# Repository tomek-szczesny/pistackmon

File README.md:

# PiStackMon

## What is it?

PiStackMon started off as a hardware module for distributing power to multiple stacked Raspberry Pi computers, rathen than handling multiple USB power adapters.

Over time, with its feature list open for new ideas, it grew into a highly integrated, multi purpose board with extended connectivity options.

The most eye catching feature is the live system monitor, with three most basic parameters (Temperature, RAM and CPU) clearly presented on a LED matrix. This helps quickly diagnosing performance bottlenecks by just looking at your cluster. LEDs are driven by a lightweight daemon, *pistackmond*, that compiles and runs on any target architecture.

PiStackMon comes with a variety of extra connectivity features, such as optically isolated outputs, isolated high current switches (up to 6A), dedicated fan output with suitable transistor, not to mention the usual I2C, UART or SPI.

Finally, PiStackMon allows you to power your SBC via GPIO pins, with additional polyfuse protection and a large capacitor, ensuring safe and stable operation. Screw terminals or barrel jack power inputs let you use any 5V power supply you wish, or even daisy chain a few units, thus sharing a common supply.

PiStackMon is compatible with any SBC following the RasPi GPIO layout. 

## Hardware

PiStackMon comes in two varieties, *lite* and *classic*.

### PiStackMon Lite

By popular demand, a new hardware version has been rolled out, offering the most useful subset of features seen in the Classic design. All mandatory SMD components are placed on top side, so the board may be ordered preassembled by JLCPCB. All required files are available in this repository.

The user is required to solder their own 40-pin socket, power switch pin header and power socket of their choice.

Features include:

- DC power input (either 5mm screw terminal or barrel jack)

- 2.5A Polyfuse protection

- 100uF ceramic capacitor

- Pin header for managing power supply (using a jumper or any other mechanical switch)

- 3x 5-LED indicators of real-time CPU usage, RAM usage and CPU temperature

- +5V LED indicator

- Extra user-programmable LED

- Soldering pads for accesing selected GPIOs:
  
  - I2C1
  
  - UART
  
  - GND, 3V3

- Two 0805 SMD placeholders for optional I2C1 pullup resistors

### PiStackMon Classic

The omnipotent, original design with all features available in the project. It is targeted at more advanced users, as no kits or preassembled units are available.

Alternatively, the schematic and KiCAD project files are available for reference. Feel free to modify it to suit your needs!

The design follows strict rules, so PCBs may be obtained for as low as 2 USD per 5 pieces at JLCPCB. 

- Supplying SBCs via screw terminals rather than USB port

- Dual power inputs-outputs allow clean and easy daisy-chaining

- 2.5A self-healing polyfuse protection 

- Bulk capacitor helps preventing transient undervoltage events

- Pin header for managing power supply (using a jumper or any other mechanical switch)

- +5V LED indicator

- 3x 5-LED indicators of real-time CPU usage, RAM usage and CPU temperature

- Auxiliary IOs for your projects:
  
  - SPI0, I2C1 and 1Wire easily accesible through 2.54mm headers
  
  - 1-Wire pullup resistor
  
  - 3-pin header with RC-filtered 3V3 supply for IR sensors
  
  - 2-pin header with 5V and BJT-reinforced low side switch, for PWM fan control
  
  - Two optically isolated outputs, for pulling external logic up or down (>2.5mA)
  
  - Two high-power, isolated low side switches, up to 26V and 6A
  
  - Alternatively, MCP1416s can be used as line drivers directly
  
  - Optical isolation lets you drive external circuits without creating ground loops
  
  - One isolated output and one high-power switch are connected to hardware PWM GPIO pins

- Low profile PCBs allow stacking with spacers as short as 20mm,

- No risk of contact with conductive stack spacers

- Components selected for low cost and relatively easy assembly (One TSSOP24 chip might be tricky)

- Alternative components are listed as well

- Modular design lets you build even cheaper boards without features you don't need

## Software

*pistackmond* is a lightweight daemon that's only purpose is to read system stats and drive PiStackMon LEDs. Additionally, it may be used by external software to drive the user-programmable LED available in PiStackMon Lite.

The recommended way to set up *pistackmond* on a target machine is to build it from source, in a few simple steps explained below. Alternatively, a DEB package may be built and distributed within your cluster.

*pistackmond* runs as a systemd service and has no dependencies outside standard C++ libraries. It has been tested on multiple Linux systems, including those based on Ubuntu, Debian or Arch.

#### Building pistackmond from source

- Log in to your SBC as any user with sudo access. 

- Install `git`, `g++` and `make`:
  
  - Debian, Ubuntu, RasPi OS etc:
    
    `sudo apt install git g++ make`
  
  - Arch, Manjaro and other derivatives:
    
    `sudo pacman -S git gcc make`

- Clone this repository:
  
  `git clone --depth 1 --branch main https://github.com/tomek-szczesny/pistackmon.git`

- Enter sw directory:
  
  - `cd pistackmon/sw`

- List build options to pick the right one for your SBC:
  
  - `make`

- Build pistackmond (Example for Raspberry Pi 4):
  
  - `make rpi4`

- Install and run systemd service
  
  - `sudo make install`

Note that you can change the default-brightness of LED-colors using the make
command, e.g. the following command changes the default 0.35 to 0.25.

    make rpi4 LED_G=0.25

The executable `pistackmond` supports various commandline arguments, see

    pistackmond -h

for a short help. Typically it is used to control the user-led (light version
only):

    pistackmond -u 1
    pistackmond -u 0
    pistackmond -u 0.4

The first command turns the blue user-led on, the second off and the third
turns it on with reduced brightness.

The `-b` option is used as a scaling factor for the overall brightness and
is only valid during service-startup. To set the factor for the service,
edit `/etc/default/pistackmond`.

That's it! PiStackMon should start displaying your computer stats immediately.

#### Creating a DEB-Package

In case you don't want to have a compiler and source code on your
production machines, you can create a deb-package on one system and
install it on multiple other systems.

The recommended procedure is:

```
apt-get -y install checkinstall  # if not already installed
cd pistackmon/sw
make clean                       # in case you don't start from scratch
#edit the `makefile` and replace `PREFIX=/usr/local` with `PREFIX=/usr`
make rpi4
sudo ./make-deb rpi4
```

This will create a package named `pistackmond-rpi4...deb`.

To install this package, run

```
dpkg -i pistackmond-rpi4...deb
sudo systemctl start pistackmond.service
```

## Compatible SBCs

PiStackMon is electrically compatible with all SBCs that follow the RasPi 40-pin GPIO layout. However, explicit support must be implemented in *pistackmond* daemon for that to work.

| SBC            | Status     | Remarks                                                                                                                                    |
| -------------- | ---------- | ------------------------------------------------------------------------------------------------------------------------------------------ |
| Raspberry Pi 3 | Compatible |                                                                                                                                            |
| Raspberry Pi 4 | Compatible |                                                                                                                                            |
| Odroid N2(+)(L)| Compatible | Powering via PiStackMon is not supported. Any attempt will likely destroy your N2.                                                         |
| Odroid C1(+)   | Compatible | Temperature sensing not confirmed. OS must export CPU temperature to the following file: `/sys/devices/virtual/thermal/thermal_zone0/temp` |
| Odroid C2      | Compatible | Powering via PiStackMon may be possible - not tested, proceed with caution.                                                                |
| Odroid M1      | Compatible | Powering via PiStackMon is not supported. Any attempt will likely destroy your M1.                                                         |

Limited amount of free PiStackMon samples is available for testers and contributors for new platforms. Open an Issue to get in touch!

# Disclaimer

This hardware and software is provided as-is.
All hardware and software presented in this repository may pose hazard to humans, animals, plants, fungi, ghosts, spirits and hardware, and is not guaranteed to work at all.
DO NOT ATTEMPT TO MAKE ANY USE OF FILES PROVIDED IN THIS REPOSITORY.

Users agree to take full responsibility for their actions involving files in this repository.
Ask an expert before you mess with stuff you don't understand.

# 

# Building PistackMon Classic

This chapter will definitely need some love, but for now just be sure to follow a few guidelines off the top of my head:

- Decide which features you need or not. As a rule of thumb, you may ignore any boxed part of a schematic independently.
- Check the datasheet of your LEDs or experiment to determine what is the optimal driving current for them. Some LEDs need 1mA, some 10mA. There are no recommended LEDs for PiStackMon.
- If different colors of your LEDs of choice have different intensities, don't worry, there are const values in the code to compensate for that.
- "NM" resistors are simply Not Mounted - leave these places empty, unlesss you want to hack PiStackMon for other purposes.
- Before you do anything, just remember that 40-pin connector should be mounted as the very last component, after you make sure everything else works. Consider it a permanent component, because removing it is indeed a pain in the rectum.
- Mount everything you plan to include, except 40-pin connector and C1. Power up your SBC using its original power input. You may test PiStackMon by carefully connecting it to SBC's GPIO header directly, and applying some tension to ensure proper connection. It is a good idea to check if all LEDs work correctly and that you picked the right LED currents.
- After soldering, make sure you clean your board _very carefully_ from any traces of flux, especially under and around the LED driver chip. Dip it in pure alcohol for an hour if you have to. Failing to do so may make some LEDs glow even though these are supposed to be off.
- Place a tiny heatsink on a low side high-power switch MOSFET if you plan to thrash the living hell out of it.

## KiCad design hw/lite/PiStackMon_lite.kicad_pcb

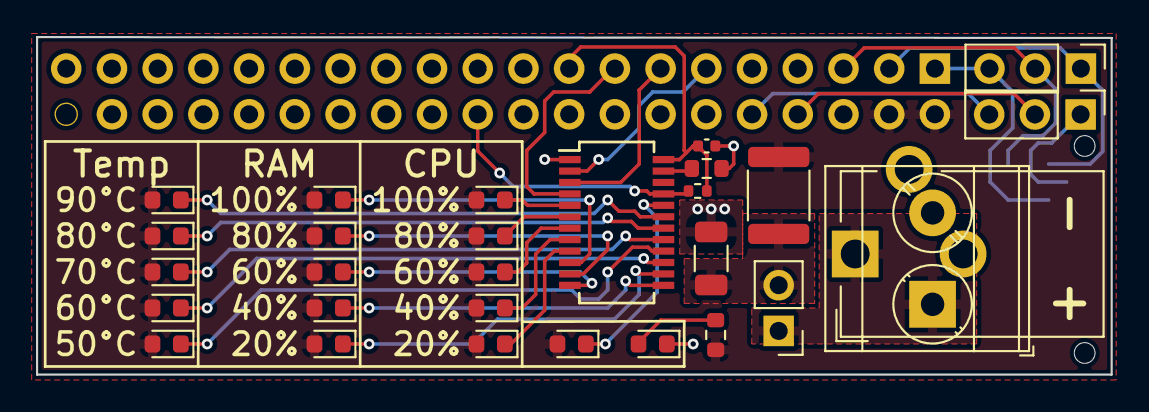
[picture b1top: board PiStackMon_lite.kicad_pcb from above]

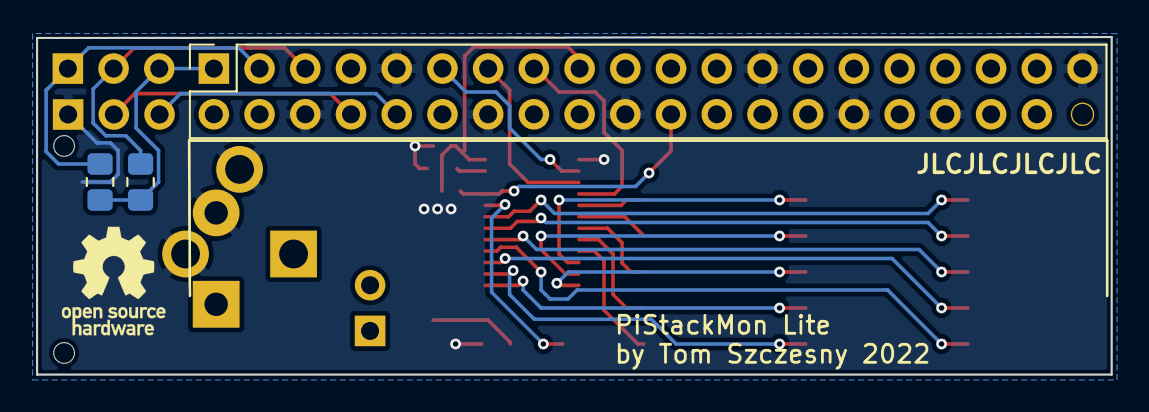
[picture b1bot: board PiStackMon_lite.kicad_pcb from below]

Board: 2 copper layers, 59.7 x 18.8 mm, 35 parts (4 on the bottom side), 32 nets.

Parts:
C1: 100u 6.3V; C_1206_3216Metric
C2: 100n; C_0402_1005Metric
D1, D2, D3, D4, D6, D7, D8, D14, D15, D16: G; LED_0603_1608Metric
D5, D9, D13: Y; LED_0603_1608Metric
D10, D11, D12: R; LED_0603_1608Metric
D17: B; LED_0603_1608Metric
F1: SMD1812B260TF/12; Fuse_1812_4532Metric
H1, H2: Tooling Hole
J1, J2: Conn_01x03; PinHeader_1x03_P2.54mm_Vertical
J3: 5.08mm; TerminalBlock_Phoenix_MKDS-3-2-5.08_1x02_P5.08mm_Horizontal
J5: CUI PJ-102; BarrelJack_CUI_PJ-102AH_Horizontal
JP1: PWR; PinHeader_1x02_P2.54mm_Vertical
LOGO1: Logo_Open_Hardware_Small; OSHW-Logo_5.7x6mm_SilkScreen
P1: Conn_02x20_Odd_Even; PinSocket_2x20_P2.54mm_Vertical
R1, R4: NM; R_0805_2012Metric_Pad1.20x1.40mm_HandSolder
R2: 10k; R_0603_1608Metric
R3: 560R; R_0603_1608Metric
R5: 3k3; R_0402_1005Metric
U1: TLC59282DBQR; SSOP-24_3.9x8.7mm_P0.635mm

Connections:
+3V3: C2.1, P1.17, R5.2, U1.24 (VDD)
+5V: D1.2 (A), D2.2 (A), D3.2 (A), D4.2 (A), D5.2 (A), D6.2 (A), D7.2 (A), D8.2 (A), D9.2 (A), D10.2 (A), D11.2 (A), D12.2 (A), D13.2 (A), D14.2 (A), D15.2 (A), D17.2 (A), F1.1, P1.2, P1.4, R3.1
+5VP: J3.1, J5.1, JP1.1 (A)
/3V3_2: J1.3, P1.1, R1.1, R4.1
/GPIO2(SDA1): J1.1, P1.3, R4.2
/GPIO3(SCL1): J1.2, P1.5, R1.2
/GPIO14(TXD0): J2.2, P1.8
/GPIO15(RXD0): J2.3, P1.10
/GPIO17(GEN0): P1.11, U1.2 (SDI)
/GPIO22(GEN3): P1.15, U1.4 (LE/DM1)
/GPIO25(GEN6): P1.22, R5.1, U1.21 (~OE/DM2)
/GPIO27(GEN2): P1.13, U1.3 (CLK)
GND: C1.2, C2.2, D16.1 (K), J2.1, J3.2, J5.2, J5.3, P1.6, P1.9, P1.14, P1.20, P1.25, P1.30, P1.34, P1.39, R2.2, U1.1 (GND)
unnamed: C1.1, F1.2, JP1.2 (B)
unnamed: D1.1 (K), U1.9 (~OUT4)
unnamed: D2.1 (K), U1.8 (~OUT3)
unnamed: D3.1 (K), U1.7 (~OUT2)
unnamed: D4.1 (K), U1.6 (~OUT1)
unnamed: D5.1 (K), U1.5 (~OUT0)
unnamed: D6.1 (K), U1.14 (~OUT9)
unnamed: D7.1 (K), U1.13 (~OUT8)
unnamed: D8.1 (K), U1.12 (~OUT7)
unnamed: D9.1 (K), U1.11 (~OUT6)
unnamed: D10.1 (K), U1.10 (~OUT5)
unnamed: D11.1 (K), U1.19 (~OUT14)
unnamed: D12.1 (K), U1.18 (~OUT13)
unnamed: D13.1 (K), U1.17 (~OUT12)
unnamed: D14.1 (K), U1.15 (~OUT10)
unnamed: D15.1 (K), U1.16 (~OUT11)
unnamed: D16.2 (A), R3.2
unnamed: D17.1 (K), U1.20 (~OUT15)
unnamed: R2.1, U1.23 (R-EXT)

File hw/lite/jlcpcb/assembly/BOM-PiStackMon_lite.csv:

Comment,Designator,Footprint,LCSC
TLC59282DBQR,U1,SSOP-24_3.9x8.7mm_P0.635mm,C129352
100u 6.3V,C1,C_1206_3216Metric,C15008
100n,C2,C_0402_1005Metric,C1525
560R,R3,R_0603_1608Metric,C23204
10k,R2,R_0603_1608Metric,C25804
3k3,R5,R_0402_1005Metric,C25890
SMD1812B260TF/12,F1,Fuse_1812_4532Metric,C269147
Y,"D13,D5,D9",LED_0603_1608Metric,C72038
B,D17,LED_0603_1608Metric,C72041
G,"D1,D14,D15,D16,D2,D3,D4,D6,D7,D8",LED_0603_1608Metric,C72043
R,"D10,D11,D12",LED_0603_1608Metric,C72044

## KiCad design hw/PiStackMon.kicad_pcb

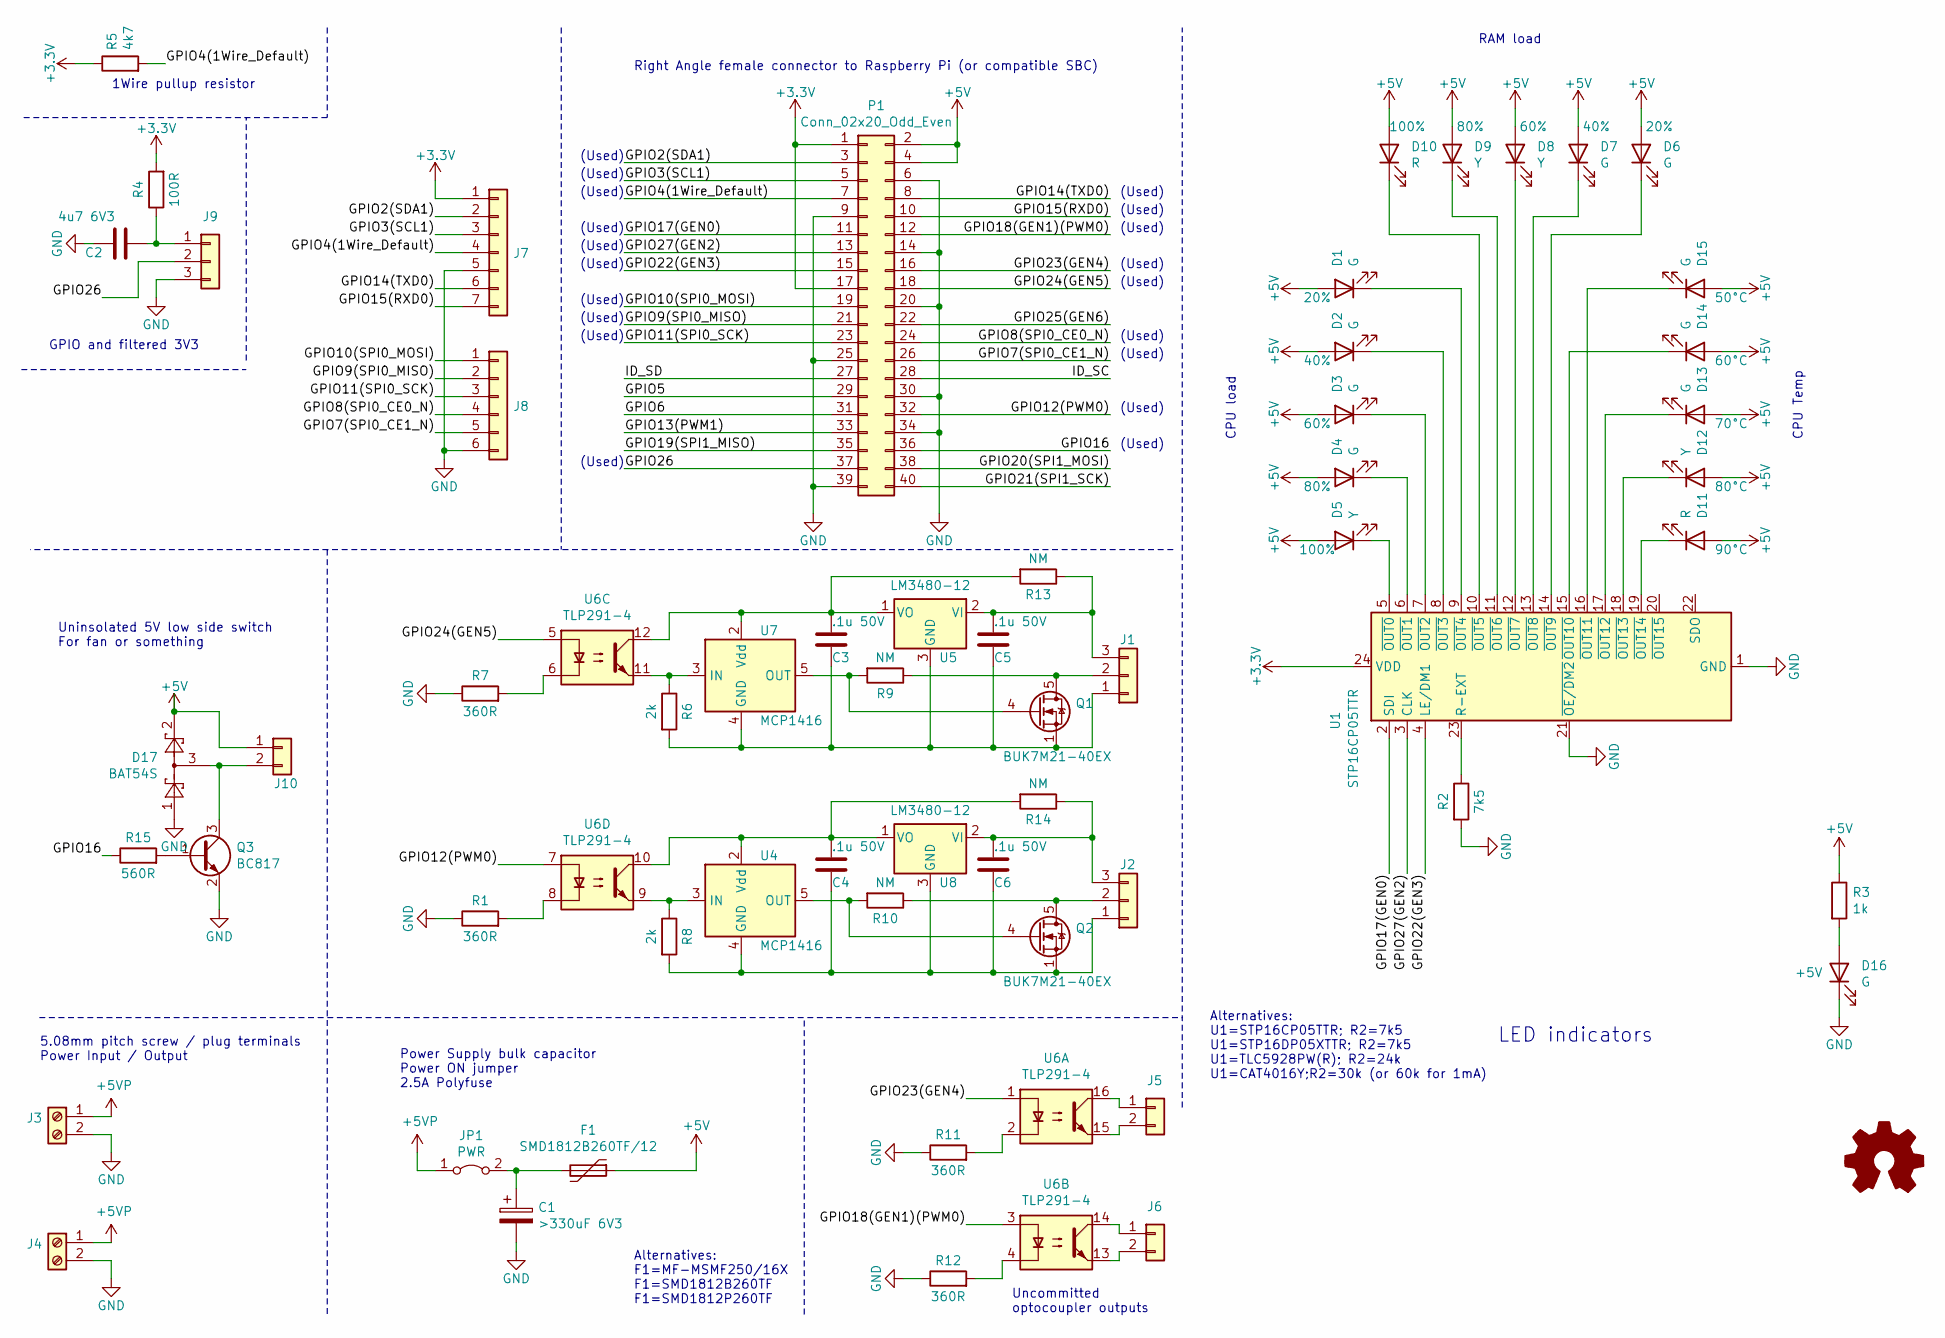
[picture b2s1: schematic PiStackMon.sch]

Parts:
C1: >330uF 6V3; CP_Radial_D8.0mm_P3.50mm
C2: 4u7 6V3; C_0603_1608Metric_Pad1.08x0.95mm_HandSolder; LCSC C8032
C3, C4, C5, C6: .1u 50V; C_0603_1608Metric_Pad1.08x0.95mm_HandSolder; LCSC C14663
D1, D2, D3, D4, D6, D7, D13, D14, D15, D16: G; LED_0603_1608Metric_Pad1.05x0.95mm_HandSolder; LCSC C72043
D5, D8, D9, D12: Y; LED_0603_1608Metric_Pad1.05x0.95mm_HandSolder; LCSC C72038
D10, D11: R; LED_0603_1608Metric_Pad1.05x0.95mm_HandSolder; LCSC C72044
D17: BAT54S; SOT-23; LCSC C47546
F1: SMD1812B260TF/12; Fuse_1812_4532Metric_Pad1.30x3.40mm_HandSolder; LCSC C269147
J1, J2, J9: Conn_01x03; PinHeader_1x03_P2.54mm_Vertical
J3, J4: Screw_Terminal_01x02; TerminalBlock_Phoenix_MKDS-3-2-5.08_1x02_P5.08mm_Horizontal
J5, J6, J10: Conn_01x02; PinHeader_1x02_P2.54mm_Vertical
J7: Conn_01x07; PinHeader_1x07_P2.54mm_Vertical
J8: Conn_01x05; PinHeader_1x06_P2.54mm_Vertical
JP1: PWR; PinHeader_1x02_P2.54mm_Vertical
LOGO1: Logo_Open_Hardware_Small; OSHW-Logo_5.7x6mm_SilkScreen
P1: Conn_02x20_Odd_Even; PinSocket_2x20_P2.54mm_Vertical
Q1, Q2: BUK7M21-40EX; LFPAK33
Q3: BC817; SOT-23; LCSC C52801
R1, R7, R11, R12: 360R; R_0603_1608Metric_Pad0.98x0.95mm_HandSolder; LCSC C25194
R2: 7k5; R_0603_1608Metric_Pad0.98x0.95mm_HandSolder; LCSC C23234
R3: 1k; R_0603_1608Metric_Pad0.98x0.95mm_HandSolder; LCSC C21190
R4: 100R; R_0603_1608Metric_Pad0.98x0.95mm_HandSolder; LCSC C22775
R5: 4k7; R_0603_1608Metric_Pad0.98x0.95mm_HandSolder; LCSC C23162
R6, R8: 2k; R_0603_1608Metric_Pad0.98x0.95mm_HandSolder; LCSC C22975
R9, R10, R13, R14: NM; R_0603_1608Metric_Pad0.98x0.95mm_HandSolder
R15: 560R; R_0603_1608Metric_Pad0.98x0.95mm_HandSolder; LCSC C23204
U1: STP16CP05TTR; TSSOP-24_4.4x7.8mm_P0.65mm; LCSC C127267
U4, U7: MCP1416; SOT-23-5; LCSC C83775
U5, U8: LM3480-12; SOT-23; LCSC C130175
U6: TLP291-4; SOIC-16_4.55x10.3mm_P1.27mm; LCSC C60900

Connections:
+3V3: J7.1, P1.1, P1.17, R4.2, R5.1, U1.24 (VDD)
+5V: D1.2 (A), D2.2 (A), D3.2 (A), D4.2 (A), D5.2 (A), D6.2 (A), D7.2 (A), D8.2 (A), D9.2 (A), D10.2 (A), D11.2 (A), D12.2 (A), D13.2 (A), D14.2 (A), D15.2 (A), D17.2, F1.1, J10.1, P1.2, P1.4, R3.1
+5VP: J3.1, J4.1, JP1.1 (A)
/GPIO2(SDA1): J7.2, P1.3
/GPIO3(SCL1): J7.3, P1.5
/GPIO4(1Wire_Default): J7.4, P1.7, R5.2
/GPIO5: P1.29
/GPIO6: P1.31
/GPIO7(SPI0_CE1_N): J8.5, P1.26
/GPIO8(SPI0_CE0_N): J8.4, P1.24
/GPIO9(SPI0_MISO): J8.2, P1.21
/GPIO10(SPI0_MOSI): J8.1, P1.19
/GPIO11(SPI0_SCK): J8.3, P1.23
/GPIO12(PWM0): P1.32, U6.7
/GPIO13(PWM1): P1.33
/GPIO14(TXD0): J7.6, P1.8
/GPIO15(RXD0): J7.7, P1.10
/GPIO16: P1.36, R15.1
/GPIO17(GEN0): P1.11, U1.2 (SDI)
/GPIO18(GEN1)(PWM0): P1.12, U6.3
/GPIO19(SPI1_MISO): P1.35
/GPIO20(SPI1_MOSI): P1.38
/GPIO21(SPI1_SCK): P1.40
/GPIO22(GEN3): P1.15, U1.4 (LE/DM1)
/GPIO23(GEN4): P1.16, U6.1
/GPIO24(GEN5): P1.18, U6.5
/GPIO25(GEN6): P1.22
/GPIO26: J9.2, P1.37
/GPIO27(GEN2): P1.13, U1.3 (CLK)
/ID_SC: P1.28
/ID_SD: P1.27
GND: C1.2, C2.2, D16.1 (K), D17.1, J3.2, J4.2, J7.5, J8.6, J9.3, P1.6, P1.9, P1.14, P1.20, P1.25, P1.30, P1.34, P1.39, Q3.2 (E), R1.1, R2.2, R7.1, R11.1, R12.1, U1.1 (GND), U1.21 (~OE/DM2)
unnamed: C1.1, F1.2, JP1.2 (B)
unnamed: C2.1, J9.1, R4.1
unnamed: C3.1, R13.2, U5.1 (VO), U6.12, U7.2 (Vdd)
unnamed: C3.2, C5.2, J1.1, Q1.1 (S), Q1.2 (S), Q1.3 (S), R6.2, U5.3 (GND), U7.4 (GND)
unnamed: C4.1, R14.2, U4.2 (Vdd), U6.10, U8.1 (VO)
unnamed: C4.2, C6.2, J2.1, Q2.1 (S), Q2.2 (S), Q2.3 (S), R8.2, U4.4 (GND), U8.3 (GND)
unnamed: C5.1, J1.3, R13.1, U5.2 (VI)
unnamed: C6.1, J2.3, R14.1, U8.2 (VI)
unnamed: D1.1 (K), U1.9 (~OUT4)
unnamed: D2.1 (K), U1.8 (~OUT3)
unnamed: D3.1 (K), U1.7 (~OUT2)
unnamed: D4.1 (K), U1.6 (~OUT1)
unnamed: D5.1 (K), U1.5 (~OUT0)
unnamed: D6.1 (K), U1.14 (~OUT9)
unnamed: D7.1 (K), U1.13 (~OUT8)
unnamed: D8.1 (K), U1.12 (~OUT7)
unnamed: D9.1 (K), U1.11 (~OUT6)
unnamed: D10.1 (K), U1.10 (~OUT5)
unnamed: D11.1 (K), U1.19 (~OUT14)
unnamed: D12.1 (K), U1.18 (~OUT13)
unnamed: D13.1 (K), U1.17 (~OUT12)
unnamed: D14.1 (K), U1.15 (~OUT10)
unnamed: D15.1 (K), U1.16 (~OUT11)
unnamed: D16.2 (A), R3.2
unnamed: D17.3, J10.2, Q3.3 (C)
unnamed: J1.2, Q1.5 (D), R9.1
unnamed: J2.2, Q2.5 (D), R10.1
unnamed: J5.1, U6.16
unnamed: J5.2, U6.15
unnamed: J6.1, U6.14
unnamed: J6.2, U6.13
unnamed: Q1.4 (G), R9.2, U7.5 (OUT)
unnamed: Q2.4 (G), R10.2, U4.5 (OUT)
unnamed: Q3.1 (B), R15.2
unnamed: R1.2, U6.8
unnamed: R2.1, U1.23 (R-EXT)
unnamed: R6.1, U6.11, U7.3 (IN)
unnamed: R7.2, U6.6
unnamed: R8.1, U4.3 (IN), U6.9
unnamed: R11.2, U6.2
unnamed: R12.2, U6.4

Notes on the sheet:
Right Angle female connector to Raspberry Pi (or compatible SBC)
5.08mm pitch screw / plug terminals Power Input / Output
Power Supply bulk capacitor Power ON jumper 2.5A Polyfuse
LED indicators
CPU load
RAM load
CPU Temp
(Used)
Uncommitted optocoupler outputs
1Wire pullup resistor
GPIO and filtered 3V3
Uninsolated 5V low side switch For fan or something
Alternatives: U1=STP16CP05TTR; R2=7k5 U1=STP16DP05XTTR; R2=7k5 U1=TLC5928PW(R); R2=24k U1=CAT4016Y;R2=30k (or 60k for 1mA)
Alternatives: F1=MF-MSMF250/16X F1=SMD1812B260TF F1=SMD1812P260TF

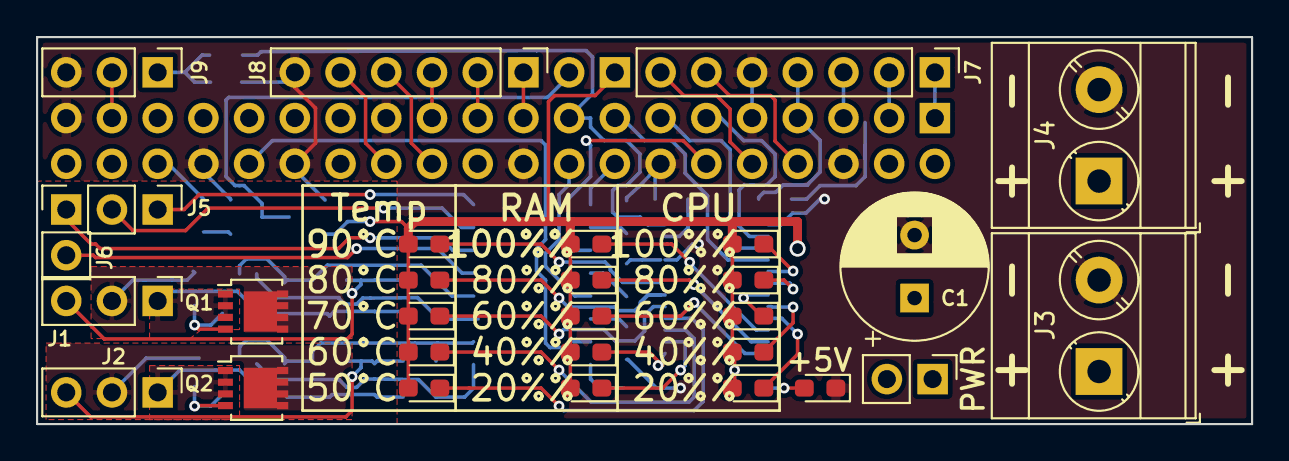
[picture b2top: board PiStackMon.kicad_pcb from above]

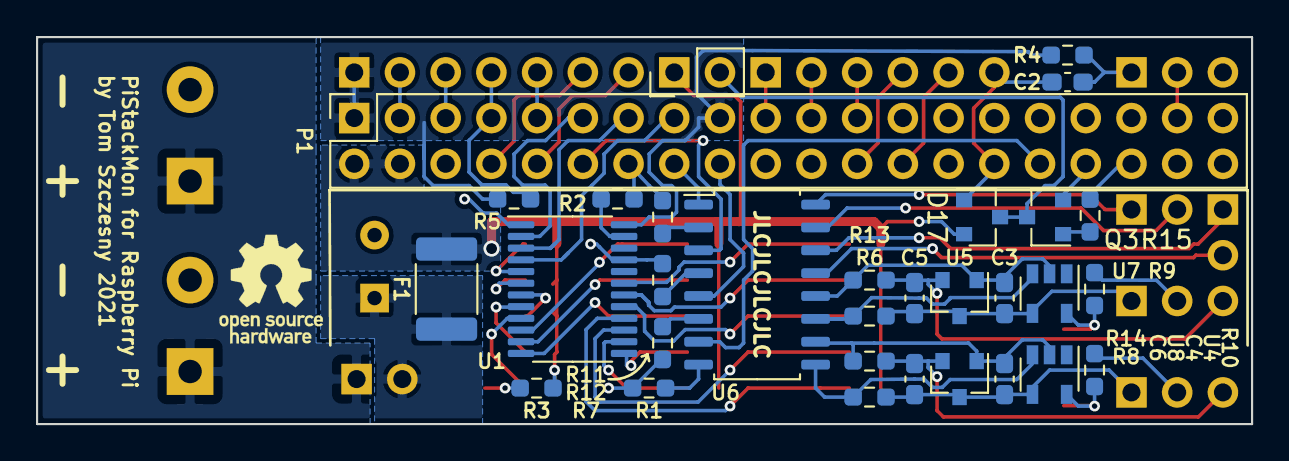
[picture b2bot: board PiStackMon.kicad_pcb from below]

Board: 2 copper layers, 67.5 x 21.5 mm, 61 parts (32 on the bottom side), 64 nets.

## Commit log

2021-03-02 Initial release - 1.0
2021-03-02 Pretending this project is awesome ;)
2021-03-02 Another picture to gaze upon!
2021-03-02 Updated comments in sw code
2021-03-03 Improved 3D model of hw, new renders
2021-03-03 Feature list update (too many of them!)
2021-03-04 RPi4 support
2021-03-04 Tweaks for underclocked Pis (200MHz)
2021-03-14 Added "make uninstall"
2021-03-14 g++ optimizations
2021-03-20 reverting build optimizations (no effect)
2021-03-25 Removing systemd service upon uninstallation
2021-03-25 corrected typo in makefile/uninstall
2021-03-25 Fix for rapid CPU blinking on startup
2021-03-25 Removing leftover debug lines
2021-03-27 More alt components; JLC assembly component codes
2021-04-06 Mutex protection of pwm_data (possible fix for std::bad_alloc)
2021-04-08 Another PWM tweak
2021-04-10 Late RTC sync fix
    The issue was present with my first Pi connected to Internet via WiFi. As the connection is estabilished later in boot time, so is the RTC synced later.
    When the clock was adjusted, the pistackomd's real time process hogged CPU for about 20 minutes to catch up with 50 years worth of sw PWM with no sleep.
2021-04-29 Added fabrication pdfs
2021-04-29 Cleaned up the fabrication data on PCB
2021-05-06 "allon" and "alloff" LED test modes
2021-05-06 Disabled initial LED test
2021-05-08 Colors of some LEDs changed; More information about adjusting LED currents
    Temperature monitor LEDs have been changed to reflect 70 deg as a warning temperature (yellow), since some RPi models apply soft throttling above 60 deg. Also running Pi at 70 deg and beyond is proba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
    RAM indicator sees color change to green at 60% level, since this is not really a state worth warning just yet.
    More R2 values are provided on the schematic to let the user pick all sorts of LED currents.
2021-05-08 Updated schematic PDF
2021-06-30 Random segfault fix (Almost certain)
2021-06-30 Added gerber files for direct manufacturing
2021-10-03 Update README.md
    Added instructions for Manjaro
2021-11-07 Update README.md
    Update with instructions for RasPiOS
2021-11-07 Fix for long uptimes (60+ days)
2021-11-25 Support for Odroid N2(+)
2021-11-25 Fix for Rpi regression
2022-02-01 install for local-fs.target instead of multi-user.target
2022-02-03 add support for Odroid-C1(+) and tweak targets
2022-02-05 use ${MAKE} instead of "make"
2022-02-05 renamed pistackmond.service to pistackmond.service.in
2022-02-05 dynamically create service file to allow installation to a different location
2022-02-06 use 'install' for installation
2022-02-08 minor fixes to commands
2022-02-08 added support for Odroid C1(+)
2022-02-08 Moved original pistackmon hw into "classic" subdir
2022-02-08 Preliminary release of 'lite' hw
2022-02-08 updated e-mail
2022-02-10 Updating LED driver to TLC59282
2022-02-11 added section 'Creating a DEB-Package'
2022-02-12 Minor changes based on @bablokb's feedback
2022-02-13 Adding JLCPCB production files
2022-02-14 check thermal_zone0 only once
2022-02-14 syntax fix: removed trailing #endif
2022-02-17 optimize compiler-flags Passing DEBUG=on to make will compile with warnings and debug-symbols. Otherwise, production-level optimization is used.
2022-02-17 support for BLANK
2022-02-17 Mostly rewritten, that's a lot of work!
2022-02-21 added *-backups to exclude KiCAD6-backups
2022-02-21 clear LEDs before pulling BLANK down
2022-02-24 replaced type of variable user (float instead of floatLP)
2022-03-31 Odroid C2 support
2022-03-31 Adding pin-table.md to repo
2022-04-03 Preliminary Odroid M1 support (guessing game)
2022-04-03 M1 support - makefiles matter!
2022-04-05 Bug fixes, now M1 works
2022-06-04 added variable PCB
2022-06-04 fixes for lite-pcb
2022-06-05 removed *.csv
2022-06-09 refactored pistackmond rules to subdir-makefile
2022-06-09 extracted GPIO-specific code to platform-files
2022-06-09 M1 support in new GPIO code
2022-06-10 removed definition and use of PCB-variable
2022-06-16 link with librt
2022-06-16 implement user-led control via shared-memory
2022-06-24 link to images of lite and classic pcb
2022-06-25 LED performance tweaks
2022-07-03 unlink shrmem from signal-handler for pistackmond-service
2022-07-05 Revert "unlink shrmem from signal-handler for pistackmond-service"
    This reverts commit 491d5954197e8289864cbb2f41f7fcfb871be11b.
2022-07-18 parse commandline with getopt
2022-07-18 added new mandatory option '-s'
2022-07-22 support build-time configuration of LED-brightness
2022-07-22 document makefile argument for LED-brightness
2022-07-22 implement -b brightness (runtime config of brightness)
2022-07-22 install pistackmond to prefix/bin instead of prefix/sbin
2022-07-22 configure brightness in /etc/default/pistackmond
2022-07-22 document program options
2022-08-14 Resistor values tweak (LEDs were too bright)
2022-08-14 New "usage" output; User LED value limited to 0-1
2022-08-14 Added two Odroids to README.md
2022-08-14 Adding PSM Lite schematic PDF
2022-11-09 Added support to Odroid N2L, lol
2023-10-06 added support for Pi5
